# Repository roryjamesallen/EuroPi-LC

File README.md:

# EuroPi LC
### A Low-Cost Hardware Version of the [EuroPi](https://github.com/Allen-Synthesis/EuroPi)  

Hardware specifications:
- 4x Outputs (0-10V, smoothed PWM, each with indicator LED)
- 2x Inputs (Both capable of 0-10V analogue input, 12 bit, input 1 also capable of digital input with hardware interrupt)
- 2 Knobs (12 bit)
- 2 Push buttons
- 4HP wide (20.32mm)

### What actully *is* a "EuroPi LC"?
The EuroPi LC (Low-Cost) can be essentially seen as a '[HAT](https://www.raspberrypi.com/news/introducing-raspberry-pi-hats/)', but using a XIAO RP2040 instead of a full sized Raspberry Pi. Without going into too much depth, the circuit converts the 3.3V signals that the XIAO RP2040 deals with (both for inputs and outputs) into 0-10V signals which are more useful in a Eurorack context. The knobs and buttons are just extra components added for the user to work with in their code. If you plan on just using code other people have written, then ignore all the 'HAT' stuff, and just think of the EuroPi LC as any other Eurorack module.  
  
So what does "work with" actually mean? Well, the EuroPi LC (as with the standard hardware EuroPi, lots of this information is interchangeable) is a platform that can be used to bring your ideas for new modules to life using [MicroPython](https://micropython.org/). In the same way that a Raspberry Pi HAT with some LEDs on it allows your Raspberry Pi code to interact with some LEDs, the EuroPi LC allows your XIAO RP2040 code to interact with all the other modules in your Eurorack system.  
  
For example, you can write basic scripts using commands as simple as `cv3.voltage(2)` to set CV (Control Voltage) output 4 to 2 volts, which you can then plug into another module and voila - your MicroPython script is now directly controlling another module in your rack, and you have *complete* control over what it does. Of course it can get a lot *lot* more complex than setting a single CV output to a voltage, and eventually you end up with scripts like quantizers, polyrhythmic sequencers, and complex synced LFOs.

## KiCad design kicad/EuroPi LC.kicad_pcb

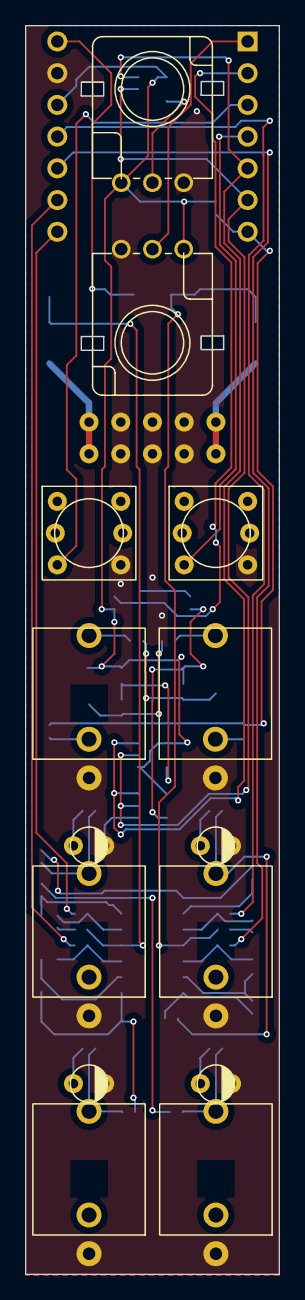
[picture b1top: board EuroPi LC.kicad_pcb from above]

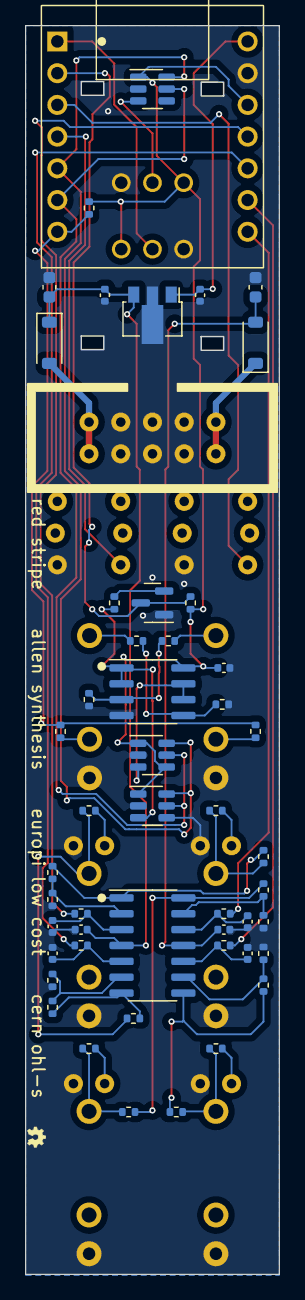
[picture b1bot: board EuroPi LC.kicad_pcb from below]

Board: 2 copper layers, 20.3 x 100.0 mm, 65 parts (51 on the bottom side), 48 nets.

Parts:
C1, C2: 10u; C_0603_1608Metric
C3, C4, C5, C6, C7, C8, C9, C10, C11: 100n; C_0402_1005Metric
D2, D3: D; D_SOD-123
J1: Conn_02x05_Odd_Even; power-header-10-pin-unlabelled
J4, J5, J6, J7, J8, J9: Thonkiconn; jack-thonkiconn-mono
LED1, LED2, LED3, LED4: LED; led-3mm
P1, P2: Potentiometer_9mm_Vertical_Linear; potentiometer-9mm
Q1: S8050; SOT-23
R1, R2, R7, R8, R11, R12, R17, R18, R27: 1K; R_0402_1005Metric
R3, R4, R13, R14: 33K; R_0402_1005Metric
R5, R6, R15, R16: 75K; R_0402_1005Metric
R9, R10, R19, R20: 5K6; R_0402_1005Metric
R21, R22, R23, R24, R28: 100K; R_0402_1005Metric
R25, R26, R29: 47K; R_0402_1005Metric
SW1, SW2: SW_Push_LED; PB01-109TL low Profile Illuminated Button
U1: TL074; SOIC-14_3.9x8.7mm_P1.27mm
U2: MCP6002-xSN; SOIC-8_3.9x4.9mm_P1.27mm
U3: SOT-89-3
U4: SEEEDUINO-XIAO; MOUDLE14P-2.54-21X17.8MM
U5, U6, U7: ADC121C027CIMK; TSOT-23-6

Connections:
+3V3: C9.1, P1.1, P2.1, R27.1, R29.1, U2.8 (V+), U4.12 (3V3), U5.1 (V_{A}), U5.4 (ADDR), U6.1 (V_{A}), U7.1 (V_{A})
+5V: C11.1, U3.1 (OUT), U4.14 (5V)
+12V: C1.1, C5.1, C10.1, D2.1 (K), U1.4 (V+), U3.3 (IN)
-12V: C2.2, C6.2, D3.2 (A), U1.11 (V-)
ADC_SCL: U4.6 (PA9_A5_D5_SCL), U5.5 (SCL), U6.5 (SCL), U7.5 (SCL)
ADC_SDA: U4.5 (PA8_A4_D4_SDA), U5.6 (SDA), U6.6 (SDA), U7.6 (SDA)
BUTTON_1: SW1.2, U4.3 (PA10_A2_D2)
BUTTON_2: SW2.2, U4.4 (PA11_A3_D3)
DIGITAL_INPUT: Q1.3 (C), R29.2, U4.2 (PA4_A1_D1)
Earth: C1.2, C2.1, C3.2, C4.2, C5.2, C6.1, C7.2, C8.2, C9.2, C10.2, C11.2, J1.3, J1.4, J1.5, J1.6, J1.7, J1.8, J4.1 (E), J5.1 (E), J6.1 (E), J7.1 (E), J8.1 (E), J9.1 (E), LED1.1 (K), LED2.1 (K), LED3.1 (K), LED4.1 (K), P1.3, P2.3, Q1.1 (E), R3.2, R4.2, R13.2, R14.2, R25.2, R26.2, SW1.4, SW2.4, U2.4 (V-), U3.2 (GND), U4.13 (GND), U5.2 (GND), U6.2 (GND), U6.4 (ADDR), U7.2 (GND)
INPUT_DETECT: R21.1, R23.1, R27.2, U4.7 (PB08_A6_D6_TX)
KNOB_1: P1.2, U7.3 (V_{IN})
KNOB_2: P2.2, U4.1 (PA02_A0_D0)
unnamed: D2.2 (A), J1.9, J1.10
unnamed: D3.1 (K), J1.1, J1.2
unnamed: J4.3 (T), R7.1, R9.2
unnamed: J5.3 (T), R8.1, R10.2
unnamed: J6.3 (T), R17.1, R19.2
unnamed: J7.3 (T), R18.1, R20.2
unnamed: J8.3 (T), R22.2
unnamed: J8.2 (TN), R21.2
unnamed: J9.3 (T), R24.2
unnamed: J9.2 (TN), R23.2
unnamed: LED1.2 (A), R9.1
unnamed: LED2.2 (A), R10.1
unnamed: LED3.2 (A), R19.1
unnamed: LED4.2 (A), R20.1
unnamed: Q1.2 (B), R28.1
unnamed: R5.2, R7.2, U1.1
unnamed: R6.2, R8.2, U1.8
unnamed: R15.2, R17.2, U1.7
unnamed: R16.2, R18.2, U1.14
unnamed: C3.1, R1.1, U1.3 (+)
unnamed: R3.1, R5.1, U1.2 (-)
unnamed: C7.1, R11.1, U1.5 (+)
unnamed: R13.1, R15.1, U1.6 (-)
unnamed: C4.1, R2.1, U1.10 (+)
unnamed: R4.1, R6.1, U1.9 (-)
unnamed: C8.1, R12.1, U1.12 (+)
unnamed: R14.1, R16.1, U1.13 (-)
unnamed: R22.1, R25.1, U2.3 (+)
unnamed: R28.2, U2.1, U2.2 (-), U6.3 (V_{IN})
unnamed: R24.1, R26.1, U2.5 (+)
unnamed: U2.6 (-), U2.7, U5.3 (V_{IN})
OUTPUT_1: R1.2, U4.11 (PA6_A10_D10_MOSI)
OUTPUT_2: R11.2, U4.10 (PA5_A9_D9_MISO)
OUTPUT_3: R2.2, U4.9 (PA7_A8_D8_SCK)
OUTPUT_4: R12.2, U4.8 (PB09_A7_D7_RX)

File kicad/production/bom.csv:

Designator,Footprint,Quantity,Value,LCSC Part #
"C1, C2",0603,2,10u,C96446
"C10, C11, C3, C4, C5, C6, C7, C8, C9",0402,9,100n,C307331
"D2, D3",D_SOD-123,2,D,C8598
J1,power-header-10-pin-unlabelled,1,Conn_02x05_Odd_Even,
"J4, J5, J6, J7, J8, J9",jack-thonkiconn-mono,6,Thonkiconn,
"LED1, LED2, LED3, LED4",led-3mm,4,LED,
"P1, P2",potentiometer-9mm,2,Potentiometer_9mm_Vertical_Linear,
Q1,SOT-23,1,S8050,
"R1, R11, R12, R17, R18, R2, R27, R7, R8",0402,9,1K,C11702
"R10, R19, R20, R9",0402,4,5K6,C25908
"R13, R14, R3, R4",0402,4,33K,C25779
"R15, R16, R5, R6",0402,4,75K,C25798
"R21, R22, R23, R24, R28",0402,5,100K,C25741
"R25, R26, R29",0402,3,47K,C25792
"SW1, SW2",PB01-109TL low Profile Illuminated Button,2,SW_Push_LED,
U1,SOIC-14_3.9x8.7mm_P1.27mm,1,TL074,
U2,SOIC-8_3.9x4.9mm_P1.27mm,1,MCP6002-xSN,
U3,SOT-89-3,1,~,C71136
U4,MOUDLE14P-2.54-21X17.8MM,1,SEEEDUINO-XIAO,
"U5, U6, U7",TSOT-23-6,3,ADC121C027CIMK,

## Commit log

2023-05-04 save
2023-06-06 kicad
2023-06-07 make 4hp
2023-06-20 input changes
    use single channel ADCs for analog inputs and knob 1 which use i2c instead of SPI to free up one pin for input 1 to be used as a digital input as well
2023-06-20 reroute pcb
2023-06-20 pcb updates
2023-06-21 add schematic notes
2023-06-25 add image
2023-06-28 add hyphen to filenames

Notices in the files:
kicad/EuroPi LC.kicad_pcb:
red stripe allen synthesis europi low cost cern ohl-s
